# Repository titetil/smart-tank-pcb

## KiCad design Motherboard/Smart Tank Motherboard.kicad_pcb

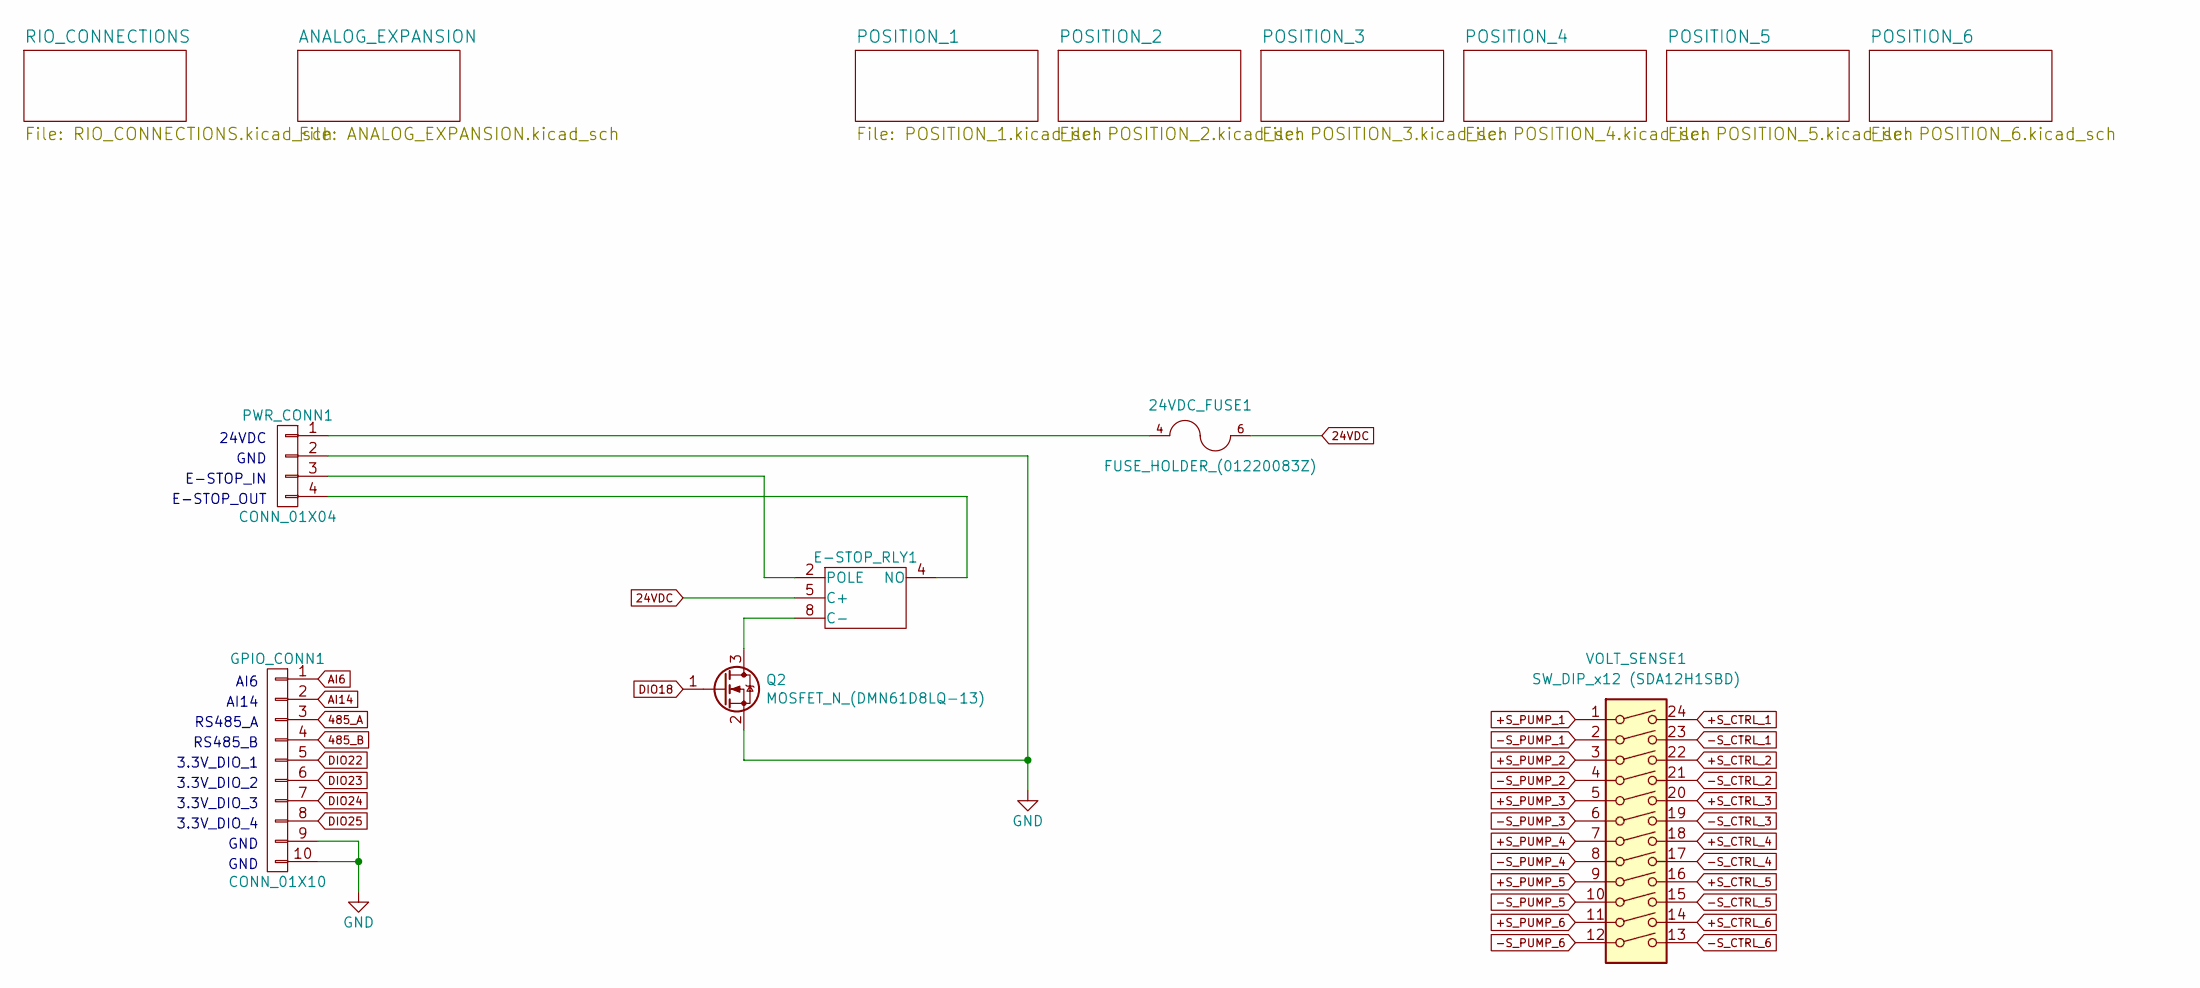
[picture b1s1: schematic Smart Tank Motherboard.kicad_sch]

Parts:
24VDC_FUSE1: FUSE_HOLDER_(01220083Z)
E-STOP_RLY1: OMRON_RELAY_(G6L-1F-DC24); OMRON_RELAY_1A_(G6L-1F-DC24)
GPIO_CONN1: CONN_01X10; PHX_TB_HDR_10_POS_STR_(1755817)
PWR_CONN1: CONN_01X04; PHX_TB_HDR_4_POS_STR_(1755752)
Q2: MOSFET_N_(DMN61D8LQ-13); SOT-23
VOLT_SENSE1: SW_DIP_x12 (SDA12H1SBD); SW_DIP_SPSTx12_(SDA12H1SBD)

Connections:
24VDC: 24VDC_FUSE1.6, 24VDC_FUSE1.7, E-STOP_RLY1.5 (C+); also elsewhere on the board
485_A: GPIO_CONN1.3; also elsewhere on the board
485_B: GPIO_CONN1.4; also elsewhere on the board
+S_CTRL_1: VOLT_SENSE1.24; also elsewhere on the board
+S_CTRL_2: VOLT_SENSE1.22; also elsewhere on the board
+S_CTRL_3: VOLT_SENSE1.20; also elsewhere on the board
+S_CTRL_4: VOLT_SENSE1.18; also elsewhere on the board
+S_CTRL_5: VOLT_SENSE1.16; also elsewhere on the board
+S_CTRL_6: VOLT_SENSE1.14; also elsewhere on the board
+S_PUMP_1: VOLT_SENSE1.1; also elsewhere on the board
+S_PUMP_2: VOLT_SENSE1.3; also elsewhere on the board
+S_PUMP_3: VOLT_SENSE1.5; also elsewhere on the board
+S_PUMP_4: VOLT_SENSE1.7; also elsewhere on the board
+S_PUMP_5: VOLT_SENSE1.9; also elsewhere on the board
+S_PUMP_6: VOLT_SENSE1.11; also elsewhere on the board
-S_CTRL_1: VOLT_SENSE1.23; also elsewhere on the board
-S_CTRL_2: VOLT_SENSE1.21; also elsewhere on the board
-S_CTRL_3: VOLT_SENSE1.19; also elsewhere on the board
-S_CTRL_4: VOLT_SENSE1.17; also elsewhere on the board
-S_CTRL_5: VOLT_SENSE1.15; also elsewhere on the board
-S_CTRL_6: VOLT_SENSE1.13; also elsewhere on the board
-S_PUMP_1: VOLT_SENSE1.2; also elsewhere on the board
-S_PUMP_2: VOLT_SENSE1.4; also elsewhere on the board
-S_PUMP_3: VOLT_SENSE1.6; also elsewhere on the board
-S_PUMP_4: VOLT_SENSE1.8; also elsewhere on the board
-S_PUMP_5: VOLT_SENSE1.10; also elsewhere on the board
-S_PUMP_6: VOLT_SENSE1.12; also elsewhere on the board
AI6: GPIO_CONN1.1; also elsewhere on the board
AI14: GPIO_CONN1.2; also elsewhere on the board
DIO18: Q2.1 (G); also elsewhere on the board
DIO22: GPIO_CONN1.5; also elsewhere on the board
DIO23: GPIO_CONN1.6; also elsewhere on the board
DIO24: GPIO_CONN1.7; also elsewhere on the board
DIO25: GPIO_CONN1.8; also elsewhere on the board
GND: GPIO_CONN1.9, GPIO_CONN1.10, PWR_CONN1.2, Q2.2 (S); also elsewhere on the board
unnamed: E-STOP_RLY1.8 (C-), Q2.3 (D)
unnamed: E-STOP_RLY1.4 (NO), PWR_CONN1.4
unnamed: E-STOP_RLY1.2 (POLE), PWR_CONN1.3
unnamed: 24VDC_FUSE1.4, 24VDC_FUSE1.5, PWR_CONN1.1

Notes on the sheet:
RS485_B
3.3V_DIO_3
RS485_A
E-STOP_IN
24VDC
GND
3.3V_DIO_4
E-STOP_OUT
3.3V_DIO_2
AI6
AI14
3.3V_DIO_1

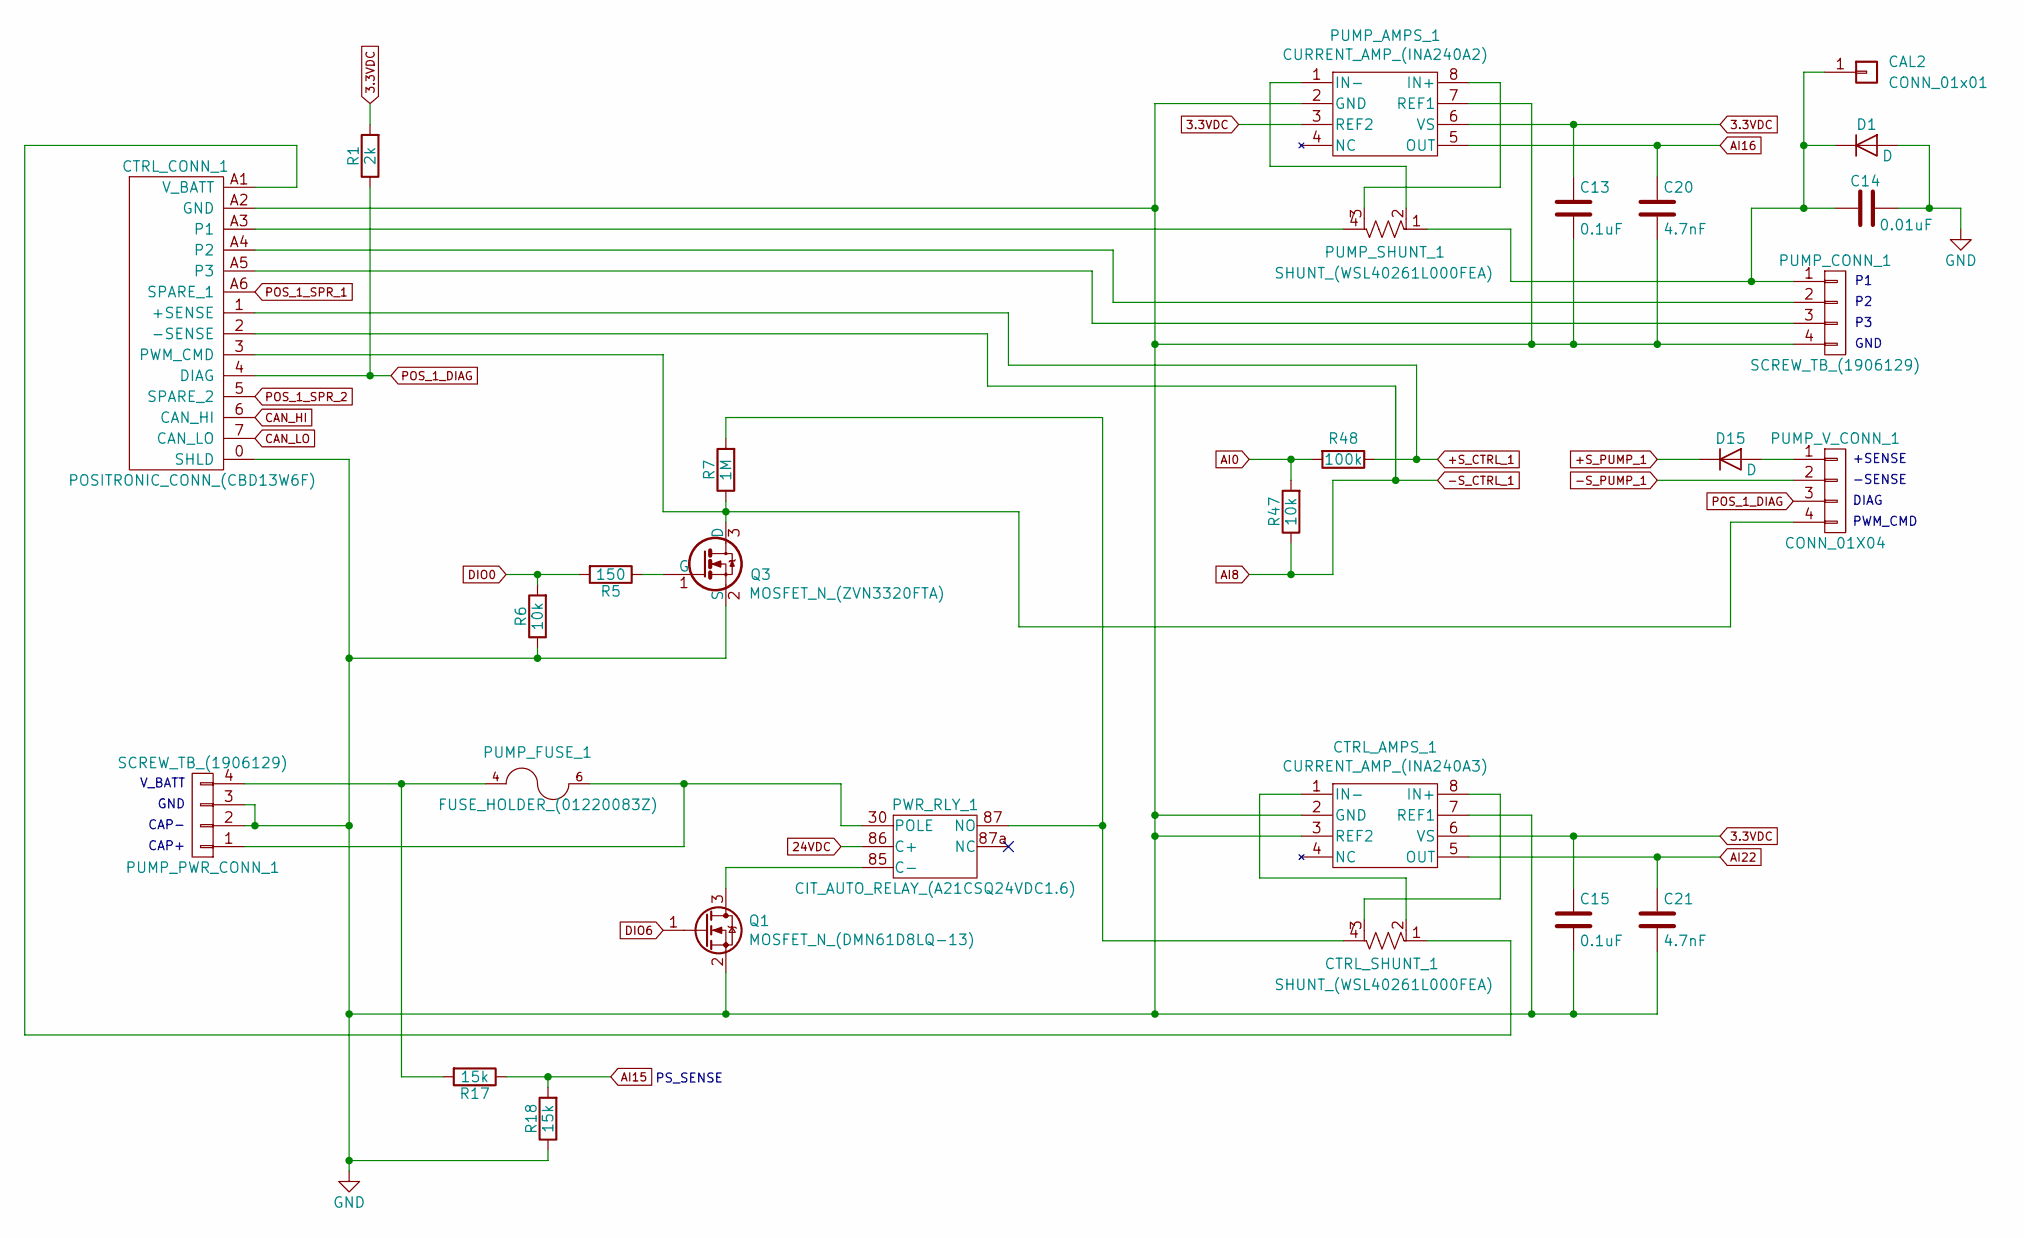
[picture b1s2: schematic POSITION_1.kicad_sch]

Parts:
C13, C15: 0.1uF; C_1206_3216Metric
C14: 0.01uF; C_1206_3216Metric
C20, C21: 4.7nF; C_1206_3216Metric
CAL2: CONN_01x01; FEMALE_SPADE_QC_(TE_63969-1)
CTRL_AMPS_1: CURRENT_AMP_(INA240A3); SOIC-8_3.9x4.9mm_P1.27mm
CTRL_CONN_1: POSITRONIC_CONN_(CBD13W6F); POSITRONIC_D-SUB_(CBD13W6F35S600X_AA)
CTRL_SHUNT_1: SHUNT_(WSL40261L000FEA)
D1, D15: D; D_SMA
PUMP_AMPS_1: CURRENT_AMP_(INA240A2); SOIC-8_3.9x4.9mm_P1.27mm
PUMP_CONN_1: SCREW_TB_(1906129); PHNX_TB_SCREW_4_POS_(1906129)
PUMP_FUSE_1: FUSE_HOLDER_(01220083Z)
PUMP_PWR_CONN_1: SCREW_TB_(1906129); PHNX_TB_SCREW_4_POS_(1906129)
PUMP_SHUNT_1: SHUNT_(WSL40261L000FEA)
PUMP_V_CONN_1: CONN_01X04; PHX_TB_HDR_4_POS_STR_(1755752)
PWR_RLY_1: CIT_AUTO_RELAY_(A21CSQ24VDC1.6); TE_AUTO_RELAY_SOCKET_(VCF4-1000)
Q1: MOSFET_N_(DMN61D8LQ-13); SOT-23
Q3: MOSFET_N_(ZVN3320FTA); SOT-23
R1: 2k; R_1206_3216Metric
R5: 150; R_1206_3216Metric
R6, R47: 10k; R_1206_3216Metric
R7: 1M; R_1206_3216Metric
R17, R18: 15k; R_1206_3216Metric
R48: 100k; R_1206_3216Metric

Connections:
3.3VDC: C13.1, C15.1, CTRL_AMPS_1.6 (VS), PUMP_AMPS_1.3 (REF2), PUMP_AMPS_1.6 (VS), R1.2; also elsewhere on the board
24VDC: PWR_RLY_1.86 (C+); also elsewhere on the board
+S_CTRL_1: CTRL_CONN_1.1 (+SENSE), R48.1; also elsewhere on the board
+S_PUMP_1: D15.1 (K); also elsewhere on the board
-S_CTRL_1: CTRL_CONN_1.2 (-SENSE), R47.1; also elsewhere on the board
-S_PUMP_1: PUMP_V_CONN_1.2; also elsewhere on the board
AI0: R47.2, R48.2; also elsewhere on the board
AI15: R17.1, R18.2; also elsewhere on the board
AI16: C20.1, PUMP_AMPS_1.5 (OUT); also elsewhere on the board
AI22: C21.1, CTRL_AMPS_1.5 (OUT); also elsewhere on the board
CAN_HI: CTRL_CONN_1.6 (CAN_HI); also elsewhere on the board
CAN_LO: CTRL_CONN_1.7 (CAN_LO); also elsewhere on the board
DIO0: R5.2, R6.2; also elsewhere on the board
DIO6: Q1.1 (G); also elsewhere on the board
GND: C13.2, C14.2, C15.2, C20.2, C21.2, CTRL_AMPS_1.2 (GND), CTRL_AMPS_1.3 (REF2), CTRL_AMPS_1.7 (REF1), CTRL_CONN_1.0 (SHLD), CTRL_CONN_1.A2 (GND), D1.2 (A), PUMP_AMPS_1.2 (GND), PUMP_AMPS_1.7 (REF1), PUMP_CONN_1.4, PUMP_PWR_CONN_1.2, PUMP_PWR_CONN_1.3, Q1.2 (S), Q3.2 (S), R6.1, R18.1; also elsewhere on the board
unnamed: C14.1, CAL2.1, D1.1 (K), PUMP_CONN_1.1, PUMP_SHUNT_1.1
unnamed: CTRL_AMPS_1.8 (IN+), CTRL_SHUNT_1.3
unnamed: CTRL_AMPS_1.1 (IN-), CTRL_SHUNT_1.2
unnamed: CTRL_CONN_1.A3 (P1), PUMP_SHUNT_1.4
unnamed: CTRL_CONN_1.A4 (P2), PUMP_CONN_1.2
unnamed: CTRL_CONN_1.A5 (P3), PUMP_CONN_1.3
unnamed: CTRL_CONN_1.3 (PWM_CMD), PUMP_V_CONN_1.4, Q3.3 (D), R7.1
unnamed: CTRL_CONN_1.A1 (V_BATT), CTRL_SHUNT_1.1
unnamed: D15.2 (A), PUMP_V_CONN_1.1
unnamed: PUMP_AMPS_1.8 (IN+), PUMP_SHUNT_1.3
unnamed: PUMP_AMPS_1.1 (IN-), PUMP_SHUNT_1.2
unnamed: PUMP_FUSE_1.6, PUMP_FUSE_1.7, PUMP_PWR_CONN_1.1, PWR_RLY_1.30 (POLE)
unnamed: PUMP_FUSE_1.4, PUMP_FUSE_1.5, PUMP_PWR_CONN_1.4, R17.2
unnamed: PWR_RLY_1.85 (C-), Q1.3 (D)
unnamed: CTRL_SHUNT_1.4, PWR_RLY_1.87 (NO), R7.2
unnamed: Q3.1 (G), R5.1
POS_1_DIAG: CTRL_CONN_1.4 (DIAG), PUMP_V_CONN_1.3, R1.1; also elsewhere on the board
POS_1_SPR_1: CTRL_CONN_1.A6 (SPARE_1); also elsewhere on the board
POS_1_SPR_2: CTRL_CONN_1.5 (SPARE_2); also elsewhere on the board

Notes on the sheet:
V_BATT
DIAG
GND
CAP-
GND
PS_SENSE
CAP+
-SENSE
+SENSE
PWM_CMD

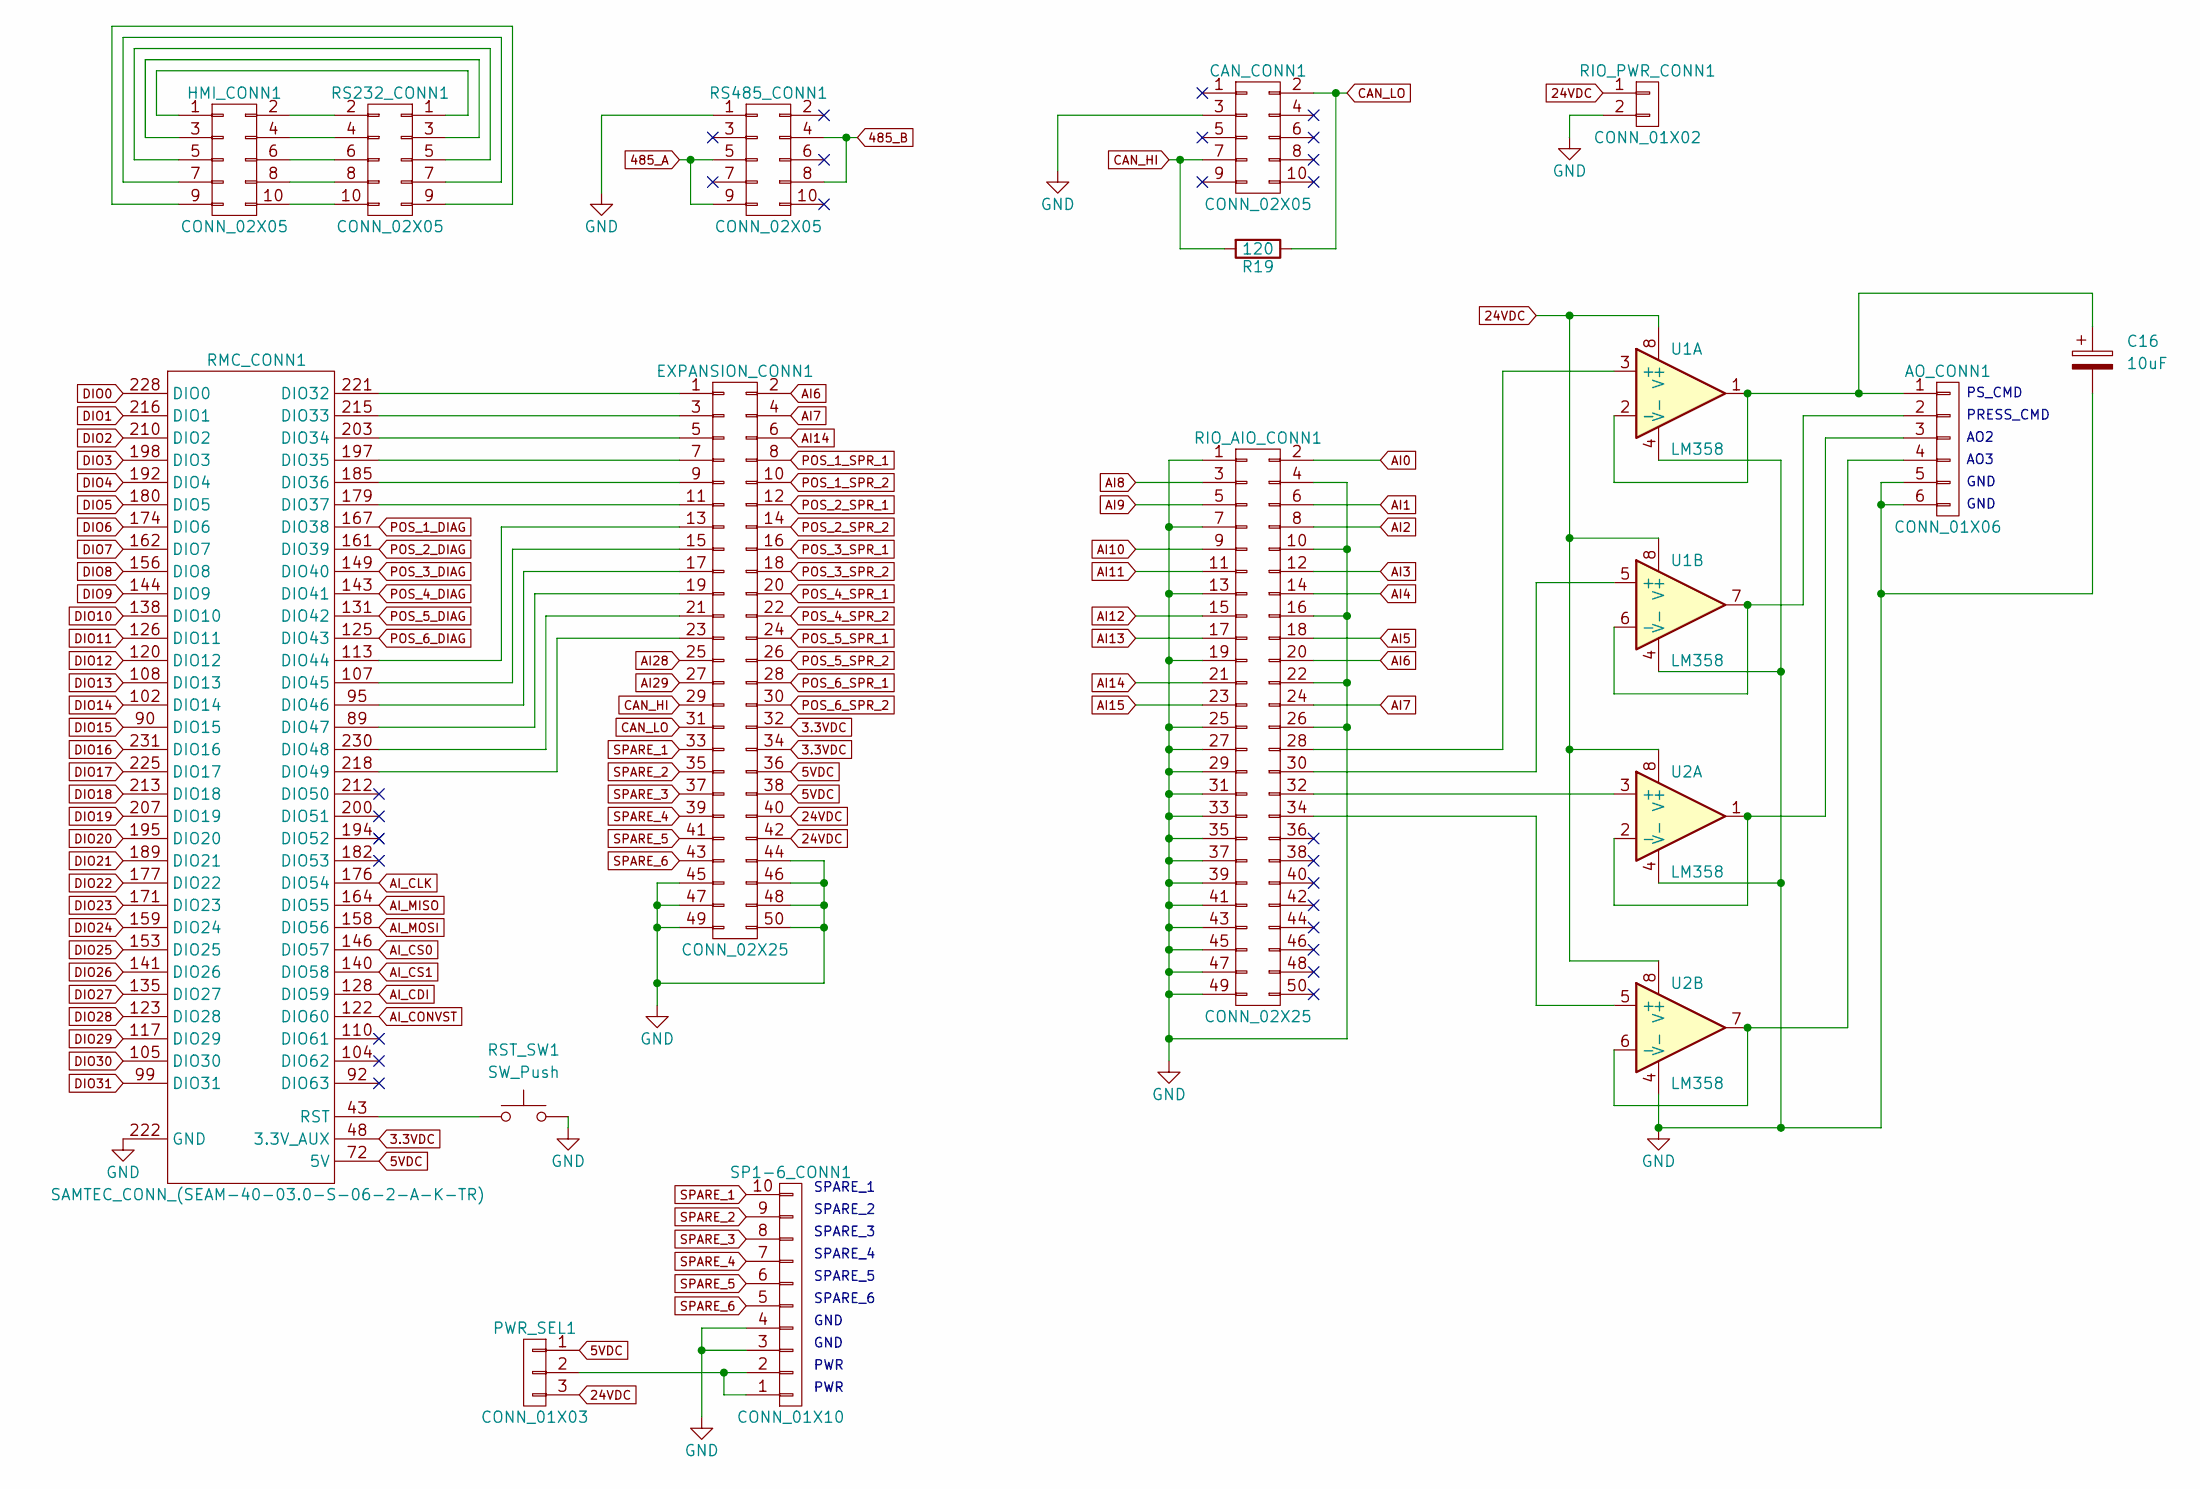
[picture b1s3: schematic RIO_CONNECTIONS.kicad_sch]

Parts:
AO_CONN1: CONN_01X06; PHX_TB_HDR_6_POS_STR_(1755778)
C16: 10uF; CAP_EEEHD1C100AR
CAN_CONN1: CONN_02X05; IDC_Header_Straight_10pins
EXPANSION_CONN1: CONN_02X25; IDC_Header_Straight_50pins
HMI_CONN1: CONN_02X05; IDC_Header_Straight_10pins
PWR_SEL1: CONN_01X03; PinHeader_1x03_P2.54mm_Vertical
R19: 120; R_1206_3216Metric
RIO_AIO_CONN1: CONN_02X25; 50-PIN_HEADER_2mm
RIO_PWR_CONN1: CONN_01X02; PHNX_TB_SCREW_2_POS_(1729128)
RMC_CONN1: SAMTEC_CONN_(SEAM-40-03.0-S-06-2-A-K-TR)
RS232_CONN1, RS485_CONN1: CONN_02X05; IDC_Header_Straight_10pins
RST_SW1: SW_Push; SW_SPST_Omron_B3FS-100xP
SP1-6_CONN1: CONN_01X10; PHX_TB_HDR_10_POS_STR_(1755817)
U1, U2: LM358; SOIC-8_3.9x4.9mm_Pitch1.27mm

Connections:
3.3VDC: EXPANSION_CONN1.32, EXPANSION_CONN1.34, RMC_CONN1.48 (3.3V_AUX); also elsewhere on the board
5VDC: EXPANSION_CONN1.36, EXPANSION_CONN1.38, PWR_SEL1.1, RMC_CONN1.54 (5V), RMC_CONN1.60 (5V), RMC_CONN1.66 (5V), RMC_CONN1.72 (5V); also elsewhere on the board
24VDC: EXPANSION_CONN1.40, EXPANSION_CONN1.42, PWR_SEL1.3, RIO_PWR_CONN1.1, U1.8 (V+), U2.8 (V+); also elsewhere on the board
485_A: RS485_CONN1.5, RS485_CONN1.9; also elsewhere on the board
485_B: RS485_CONN1.4, RS485_CONN1.8; also elsewhere on the board
-S_CTRL_1: RIO_AIO_CONN1.3; also elsewhere on the board
-S_CTRL_2: RIO_AIO_CONN1.5; also elsewhere on the board
-S_CTRL_3: RIO_AIO_CONN1.9; also elsewhere on the board
-S_CTRL_4: RIO_AIO_CONN1.11; also elsewhere on the board
-S_CTRL_5: RIO_AIO_CONN1.15; also elsewhere on the board
-S_CTRL_6: RIO_AIO_CONN1.17; also elsewhere on the board
AI0: RIO_AIO_CONN1.2; also elsewhere on the board
AI1: RIO_AIO_CONN1.6; also elsewhere on the board
AI2: RIO_AIO_CONN1.8; also elsewhere on the board
AI3: RIO_AIO_CONN1.12; also elsewhere on the board
AI4: RIO_AIO_CONN1.14; also elsewhere on the board
AI5: RIO_AIO_CONN1.18; also elsewhere on the board
AI6: EXPANSION_CONN1.2, RIO_AIO_CONN1.20; also elsewhere on the board
AI7: EXPANSION_CONN1.4, RIO_AIO_CONN1.24
AI14: EXPANSION_CONN1.6, RIO_AIO_CONN1.21; also elsewhere on the board
AI15: RIO_AIO_CONN1.23; also elsewhere on the board
AI28: EXPANSION_CONN1.25; also elsewhere on the board
AI29: EXPANSION_CONN1.27; also elsewhere on the board
AI_CDI: RMC_CONN1.128 (DIO59); also elsewhere on the board
AI_CLK: RMC_CONN1.176 (DIO54); also elsewhere on the board
AI_CONVST: RMC_CONN1.122 (DIO60); also elsewhere on the board
AI_CS0: RMC_CONN1.146 (DIO57); also elsewhere on the board
AI_CS1: RMC_CONN1.140 (DIO58); also elsewhere on the board
AI_MISO: RMC_CONN1.164 (DIO55); also elsewhere on the board
AI_MOSI: RMC_CONN1.158 (DIO56); also elsewhere on the board
CAN_HI: CAN_CONN1.7, EXPANSION_CONN1.29, R19.2; also elsewhere on the board
CAN_LO: CAN_CONN1.2, EXPANSION_CONN1.31, R19.1; also elsewhere on the board
DIO0: RMC_CONN1.228 (DIO0); also elsewhere on the board
DIO1: RMC_CONN1.216 (DIO1); also elsewhere on the board
DIO2: RMC_CONN1.210 (DIO2); also elsewhere on the board
DIO3: RMC_CONN1.198 (DIO3); also elsewhere on the board
DIO4: RMC_CONN1.192 (DIO4); also elsewhere on the board
DIO5: RMC_CONN1.180 (DIO5); also elsewhere on the board
DIO6: RMC_CONN1.174 (DIO6); also elsewhere on the board
DIO7: RMC_CONN1.162 (DIO7); also elsewhere on the board
DIO8: RMC_CONN1.156 (DIO8); also elsewhere on the board
DIO9: RMC_CONN1.144 (DIO9); also elsewhere on the board
DIO10: RMC_CONN1.138 (DIO10); also elsewhere on the board
DIO11: RMC_CONN1.126 (DIO11); also elsewhere on the board
DIO12: RMC_CONN1.120 (DIO12)
DIO13: RMC_CONN1.108 (DIO13)
DIO14: RMC_CONN1.102 (DIO14)
DIO15: RMC_CONN1.90 (DIO15)
DIO16: RMC_CONN1.231 (DIO16)
DIO17: RMC_CONN1.225 (DIO17)
DIO18: RMC_CONN1.213 (DIO18); also elsewhere on the board
DIO19: RMC_CONN1.207 (DIO19)
DIO20: RMC_CONN1.195 (DIO20)
DIO21: RMC_CONN1.189 (DIO21)
DIO22: RMC_CONN1.177 (DIO22); also elsewhere on the board
DIO23: RMC_CONN1.171 (DIO23); also elsewhere on the board
DIO24: RMC_CONN1.159 (DIO24); also elsewhere on the board
DIO25: RMC_CONN1.153 (DIO25); also elsewhere on the board
DIO26: RMC_CONN1.141 (DIO26)
DIO27: RMC_CONN1.135 (DIO27)
DIO28: RMC_CONN1.123 (DIO28)
DIO29: RMC_CONN1.117 (DIO29)
DIO30: RMC_CONN1.105 (DIO30)
DIO31: RMC_CONN1.99 (DIO31)
GND: AO_CONN1.5, AO_CONN1.6, C16.2, CAN_CONN1.3, EXPANSION_CONN1.44, EXPANSION_CONN1.45, EXPANSION_CONN1.46, EXPANSION_CONN1.47, EXPANSION_CONN1.48, EXPANSION_CONN1.49, EXPANSION_CONN1.50, RIO_AIO_CONN1.1, RIO_AIO_CONN1.4, RIO_AIO_CONN1.7, RIO_AIO_CONN1.10, RIO_AIO_CONN1.13, RIO_AIO_CONN1.16, RIO_AIO_CONN1.19, RIO_AIO_CONN1.22, RIO_AIO_CONN1.25, RIO_AIO_CONN1.26, RIO_AIO_CONN1.27, RIO_AIO_CONN1.29, RIO_AIO_CONN1.31, RIO_AIO_CONN1.33, RIO_AIO_CONN1.35, RIO_AIO_CONN1.37, RIO_AIO_CONN1.39, RIO_AIO_CONN1.41, RIO_AIO_CONN1.43, RIO_AIO_CONN1.45, RIO_AIO_CONN1.47, RIO_AIO_CONN1.49, RIO_PWR_CONN1.2, RMC_CONN1.26 (GND), RMC_CONN1.30 (GND), RMC_CONN1.36 (GND), RMC_CONN1.39 (GND), RMC_CONN1.41 (GND), RMC_CONN1.44 (GND), RMC_CONN1.47 (GND), RMC_CONN1.57 (GND), RMC_CONN1.62 (GND), RMC_CONN1.65 (GND), RMC_CONN1.75 (GND), RMC_CONN1.78 (GND), RMC_CONN1.80 (GND), RMC_CONN1.83 (GND), RMC_CONN1.93 (GND), RMC_CONN1.96 (GND), RMC_CONN1.98 (GND), RMC_CONN1.101 (GND), RMC_CONN1.111 (GND), RMC_CONN1.114 (GND), RMC_CONN1.116 (GND), RMC_CONN1.119 (GND), RMC_CONN1.129 (GND), RMC_CONN1.132 (GND), RMC_CONN1.134 (GND), RMC_CONN1.137 (GND), RMC_CONN1.147 (GND), RMC_CONN1.150 (GND), RMC_CONN1.152 (GND), RMC_CONN1.155 (GND), RMC_CONN1.165 (GND), RMC_CONN1.168 (GND), RMC_CONN1.170 (GND), RMC_CONN1.173 (GND), RMC_CONN1.183 (GND), RMC_CONN1.186 (GND), RMC_CONN1.188 (GND), RMC_CONN1.191 (GND), RMC_CONN1.201 (GND), RMC_CONN1.204 (GND), RMC_CONN1.206 (GND), RMC_CONN1.209 (GND), RMC_CONN1.219 (GND), RMC_CONN1.222 (GND), RMC_CONN1.224 (GND), RMC_CONN1.227 (GND), RMC_CONN1.237 (GND), RS485_CONN1.1, RST_SW1.2, SP1-6_CONN1.3, SP1-6_CONN1.4, U1.4 (V-), U2.4 (V-); also elsewhere on the board
unnamed: AO_CONN1.1, C16.1, U1.1, U1.2 (-)
unnamed: AO_CONN1.2, U1.6 (-), U1.7
unnamed: AO_CONN1.3, U2.1, U2.2 (-)
unnamed: AO_CONN1.4, U2.6 (-), U2.7
unnamed: EXPANSION_CONN1.1, RMC_CONN1.221 (DIO32)
unnamed: EXPANSION_CONN1.3, RMC_CONN1.215 (DIO33)
unnamed: EXPANSION_CONN1.5, RMC_CONN1.203 (DIO34)
unnamed: EXPANSION_CONN1.7, RMC_CONN1.197 (DIO35)
unnamed: EXPANSION_CONN1.9, RMC_CONN1.185 (DIO36)
unnamed: EXPANSION_CONN1.11, RMC_CONN1.179 (DIO37)
unnamed: EXPANSION_CONN1.13, RMC_CONN1.113 (DIO44)
unnamed: EXPANSION_CONN1.15, RMC_CONN1.107 (DIO45)
unnamed: EXPANSION_CONN1.17, RMC_CONN1.95 (DIO46)
unnamed: EXPANSION_CONN1.19, RMC_CONN1.89 (DIO47)
unnamed: EXPANSION_CONN1.21, RMC_CONN1.230 (DIO48)
unnamed: EXPANSION_CONN1.23, RMC_CONN1.218 (DIO49)
unnamed: HMI_CONN1.1, RS232_CONN1.1
unnamed: HMI_CONN1.2, RS232_CONN1.2
unnamed: HMI_CONN1.3, RS232_CONN1.3
unnamed: HMI_CONN1.4, RS232_CONN1.4
unnamed: HMI_CONN1.5, RS232_CONN1.5
unnamed: HMI_CONN1.6, RS232_CONN1.6
unnamed: HMI_CONN1.7, RS232_CONN1.7
unnamed: HMI_CONN1.8, RS232_CONN1.8
unnamed: HMI_CONN1.9, RS232_CONN1.9
unnamed: HMI_CONN1.10, RS232_CONN1.10
unnamed: PWR_SEL1.2, SP1-6_CONN1.1, SP1-6_CONN1.2
unnamed: RIO_AIO_CONN1.28, U1.3 (+)
unnamed: RIO_AIO_CONN1.30, U1.5 (+)
unnamed: RIO_AIO_CONN1.32, U2.3 (+)
unnamed: RIO_AIO_CONN1.34, U2.5 (+)
unnamed: RMC_CONN1.43 (RST), RST_SW1.1
POS_1_DIAG: RMC_CONN1.167 (DIO38); also elsewhere on the board
POS_1_SPR_1: EXPANSION_CONN1.8; also elsewhere on the board
POS_1_SPR_2: EXPANSION_CONN1.10; also elsewhere on the board
POS_2_DIAG: RMC_CONN1.161 (DIO39); also elsewhere on the board
POS_2_SPR_1: EXPANSION_CONN1.12; also elsewhere on the board
POS_2_SPR_2: EXPANSION_CONN1.14; also elsewhere on the board
POS_3_DIAG: RMC_CONN1.149 (DIO40); also elsewhere on the board
POS_3_SPR_1: EXPANSION_CONN1.16; also elsewhere on the board
POS_3_SPR_2: EXPANSION_CONN1.18; also elsewhere on the board
POS_4_DIAG: RMC_CONN1.143 (DIO41); also elsewhere on the board
POS_4_SPR_1: EXPANSION_CONN1.20; also elsewhere on the board
POS_4_SPR_2: EXPANSION_CONN1.22; also elsewhere on the board
POS_5_DIAG: RMC_CONN1.131 (DIO42); also elsewhere on the board
POS_5_SPR_1: EXPANSION_CONN1.24; also elsewhere on the board
POS_5_SPR_2: EXPANSION_CONN1.26; also elsewhere on the board
POS_6_DIAG: RMC_CONN1.125 (DIO43); also elsewhere on the board
POS_6_SPR_1: EXPANSION_CONN1.28; also elsewhere on the board
POS_6_SPR_2: EXPANSION_CONN1.30; also elsewhere on the board
SPARE_1: EXPANSION_CONN1.33, SP1-6_CONN1.10
SPARE_2: EXPANSION_CONN1.35, SP1-6_CONN1.9
SPARE_3: EXPANSION_CONN1.37, SP1-6_CONN1.8
SPARE_4: EXPANSION_CONN1.39, SP1-6_CONN1.7
SPARE_5: EXPANSION_CONN1.41, SP1-6_CONN1.6
SPARE_6: EXPANSION_CONN1.43, SP1-6_CONN1.5

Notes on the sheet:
SPARE_6
SPARE_1
PS_CMD
GND
SPARE_3
AO3
PRESS_CMD
PWR
AO2
SPARE_4
SPARE_5
SPARE_2

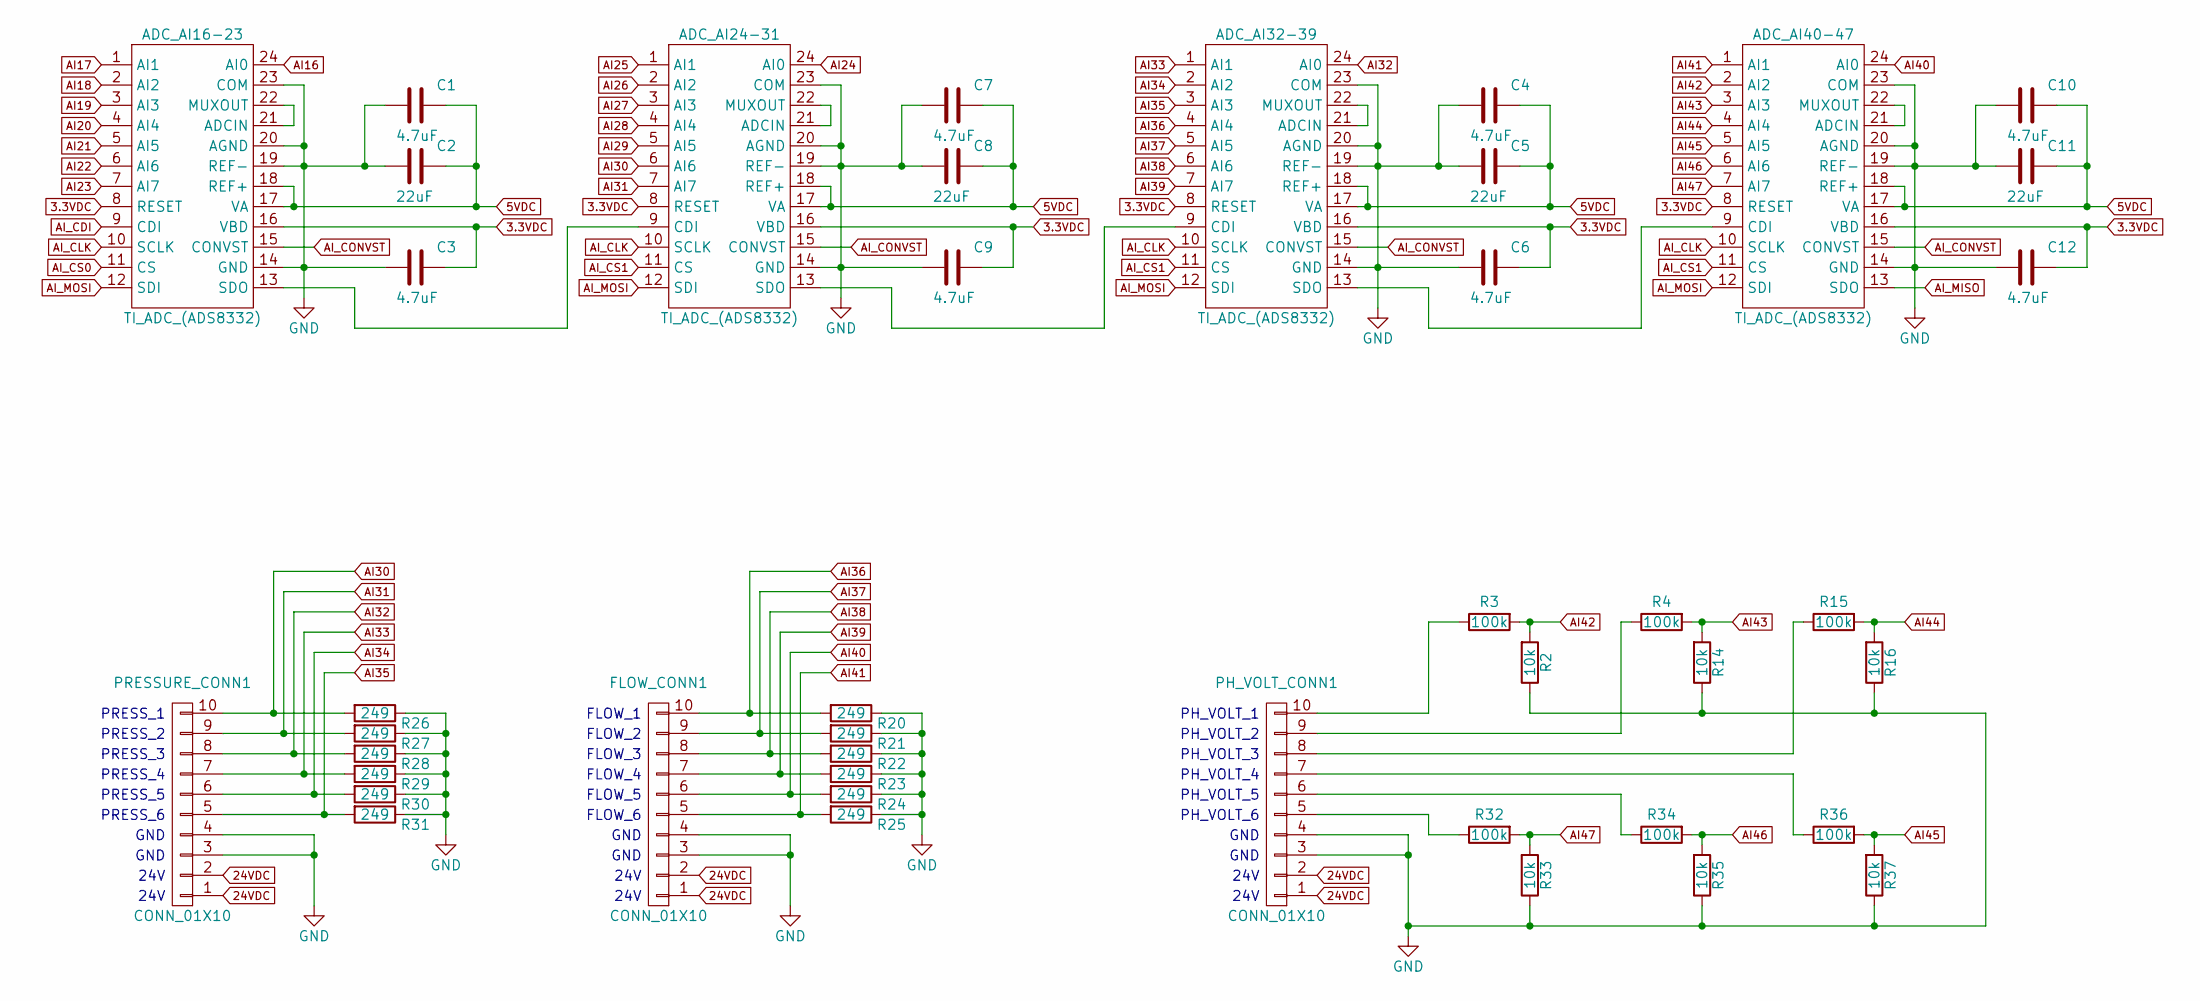
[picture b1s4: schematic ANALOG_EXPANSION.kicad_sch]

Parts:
ADC_AI16-23, ADC_AI24-31, ADC_AI32-39, ADC_AI40-47: TI_ADC_(ADS8332)
C1, C3, C4, C6, C7, C9, C10, C12: 4.7uF; C_1206_3216Metric
C2, C5, C8, C11: 22uF; C_1206_3216Metric
FLOW_CONN1: CONN_01X10; PHX_TB_HDR_10_POS_STR_(1755817)
PH_VOLT_CONN1: CONN_01X10; PHX_TB_HDR_10_POS_STR_(1755817)
PRESSURE_CONN1: CONN_01X10; PHX_TB_HDR_10_POS_STR_(1755817)
R2, R14, R16, R33, R35, R37: 10k; R_1206_3216Metric
R3, R4, R15, R32, R34, R36: 100k; R_1206_3216Metric
R20, R21, R22, R23, R24, R25, R26, R27, R28, R29, R30, R31: 249; R_1206_3216Metric

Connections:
3.3VDC: ADC_AI16-23.8 (RESET), ADC_AI16-23.16 (VBD), ADC_AI24-31.8 (RESET), ADC_AI24-31.16 (VBD), ADC_AI32-39.8 (RESET), ADC_AI32-39.16 (VBD), ADC_AI40-47.8 (RESET), ADC_AI40-47.16 (VBD), C3.1, C6.1, C9.1, C12.1; also elsewhere on the board
5VDC: ADC_AI16-23.17 (VA), ADC_AI16-23.18 (REF+), ADC_AI24-31.17 (VA), ADC_AI24-31.18 (REF+), ADC_AI32-39.17 (VA), ADC_AI32-39.18 (REF+), ADC_AI40-47.17 (VA), ADC_AI40-47.18 (REF+), C1.1, C2.1, C4.1, C5.1, C7.1, C8.1, C10.1, C11.1; also elsewhere on the board
24VDC: FLOW_CONN1.1, FLOW_CONN1.2, PH_VOLT_CONN1.1, PH_VOLT_CONN1.2, PRESSURE_CONN1.1, PRESSURE_CONN1.2; also elsewhere on the board
AI16: ADC_AI16-23.24 (AI0); also elsewhere on the board
AI17: ADC_AI16-23.1 (AI1); also elsewhere on the board
AI18: ADC_AI16-23.2 (AI2); also elsewhere on the board
AI19: ADC_AI16-23.3 (AI3); also elsewhere on the board
AI20: ADC_AI16-23.4 (AI4); also elsewhere on the board
AI21: ADC_AI16-23.5 (AI5); also elsewhere on the board
AI22: ADC_AI16-23.6 (AI6); also elsewhere on the board
AI23: ADC_AI16-23.7 (AI7); also elsewhere on the board
AI24: ADC_AI24-31.24 (AI0); also elsewhere on the board
AI25: ADC_AI24-31.1 (AI1); also elsewhere on the board
AI26: ADC_AI24-31.2 (AI2); also elsewhere on the board
AI27: ADC_AI24-31.3 (AI3); also elsewhere on the board
AI28: ADC_AI24-31.4 (AI4); also elsewhere on the board
AI29: ADC_AI24-31.5 (AI5); also elsewhere on the board
AI30: ADC_AI24-31.6 (AI6), PRESSURE_CONN1.10, R26.2
AI31: ADC_AI24-31.7 (AI7), PRESSURE_CONN1.9, R27.2
AI32: ADC_AI32-39.24 (AI0), PRESSURE_CONN1.8, R28.2
AI33: ADC_AI32-39.1 (AI1), PRESSURE_CONN1.7, R29.2
AI34: ADC_AI32-39.2 (AI2), PRESSURE_CONN1.6, R30.2
AI35: ADC_AI32-39.3 (AI3), PRESSURE_CONN1.5, R31.2
AI36: ADC_AI32-39.4 (AI4), FLOW_CONN1.10, R20.2
AI37: ADC_AI32-39.5 (AI5), FLOW_CONN1.9, R21.2
AI38: ADC_AI32-39.6 (AI6), FLOW_CONN1.8, R22.2
AI39: ADC_AI32-39.7 (AI7), FLOW_CONN1.7, R23.2
AI40: ADC_AI40-47.24 (AI0), FLOW_CONN1.6, R24.2
AI41: ADC_AI40-47.1 (AI1), FLOW_CONN1.5, R25.2
AI42: ADC_AI40-47.2 (AI2), R2.2, R3.2
AI43: ADC_AI40-47.3 (AI3), R4.2, R14.2
AI44: ADC_AI40-47.4 (AI4), R15.2, R16.2
AI45: ADC_AI40-47.5 (AI5), R36.2, R37.2
AI46: ADC_AI40-47.6 (AI6), R34.2, R35.2
AI47: ADC_AI40-47.7 (AI7), R32.2, R33.2
AI_CDI: ADC_AI16-23.9 (CDI); also elsewhere on the board
AI_CLK: ADC_AI16-23.10 (SCLK), ADC_AI24-31.10 (SCLK), ADC_AI32-39.10 (SCLK), ADC_AI40-47.10 (SCLK); also elsewhere on the board
AI_CONVST: ADC_AI16-23.15 (CONVST), ADC_AI24-31.15 (CONVST), ADC_AI32-39.15 (CONVST), ADC_AI40-47.15 (CONVST); also elsewhere on the board
AI_CS0: ADC_AI16-23.11 (CS); also elsewhere on the board
AI_CS1: ADC_AI24-31.11 (CS), ADC_AI32-39.11 (CS), ADC_AI40-47.11 (CS); also elsewhere on the board
AI_MISO: ADC_AI40-47.13 (SDO); also elsewhere on the board
AI_MOSI: ADC_AI16-23.12 (SDI), ADC_AI24-31.12 (SDI), ADC_AI32-39.12 (SDI), ADC_AI40-47.12 (SDI); also elsewhere on the board
GND: ADC_AI16-23.14 (GND), ADC_AI16-23.19 (REF-), ADC_AI16-23.20 (AGND), ADC_AI16-23.23 (COM), ADC_AI24-31.14 (GND), ADC_AI24-31.19 (REF-), ADC_AI24-31.20 (AGND), ADC_AI24-31.23 (COM), ADC_AI32-39.14 (GND), ADC_AI32-39.19 (REF-), ADC_AI32-39.20 (AGND), ADC_AI32-39.23 (COM), ADC_AI40-47.14 (GND), ADC_AI40-47.19 (REF-), ADC_AI40-47.20 (AGND), ADC_AI40-47.23 (COM), C1.2, C2.2, C3.2, C4.2, C5.2, C6.2, C7.2, C8.2, C9.2, C10.2, C11.2, C12.2, FLOW_CONN1.3, FLOW_CONN1.4, PH_VOLT_CONN1.3, PH_VOLT_CONN1.4, PRESSURE_CONN1.3, PRESSURE_CONN1.4, R2.1, R14.1, R16.1, R20.1, R21.1, R22.1, R23.1, R24.1, R25.1, R26.1, R27.1, R28.1, R29.1, R30.1, R31.1, R33.1, R35.1, R37.1; also elsewhere on the board
unnamed: ADC_AI16-23.21 (ADCIN), ADC_AI16-23.22 (MUXOUT)
unnamed: ADC_AI16-23.13 (SDO), ADC_AI24-31.9 (CDI)
unnamed: ADC_AI24-31.21 (ADCIN), ADC_AI24-31.22 (MUXOUT)
unnamed: ADC_AI24-31.13 (SDO), ADC_AI32-39.9 (CDI)
unnamed: ADC_AI32-39.21 (ADCIN), ADC_AI32-39.22 (MUXOUT)
unnamed: ADC_AI32-39.13 (SDO), ADC_AI40-47.9 (CDI)
unnamed: ADC_AI40-47.21 (ADCIN), ADC_AI40-47.22 (MUXOUT)
unnamed: PH_VOLT_CONN1.5, R32.1
unnamed: PH_VOLT_CONN1.6, R34.1
unnamed: PH_VOLT_CONN1.7, R36.1
unnamed: PH_VOLT_CONN1.8, R15.1
unnamed: PH_VOLT_CONN1.9, R4.1
unnamed: PH_VOLT_CONN1.10, R3.1

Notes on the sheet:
FLOW_1
PRESS_6
FLOW_3
PH_VOLT_2
PH_VOLT_5
PRESS_1
24V
PH_VOLT_6
PRESS_4
PRESS_2
PH_VOLT_3
FLOW_5
FLOW_4
PRESS_3
PRESS_5
GND
PH_VOLT_4
FLOW_2
FLOW_6
PH_VOLT_1
